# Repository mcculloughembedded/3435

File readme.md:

# The 3435
The *3435* is a 34 key split keyboard inspired by the [Clog V3](https://sammohr.dev/keyboards).
I have used it daily in a professional setting for more than a year.

## Features
* 34 key split
* Low profile - only 18mm from top of keycap to desk (including feet)
* Kailh Choc V1 low profile switches
* MX standard key spacing
* Ortholinear
* Angled columns
* Vertical key staggering
* Pinky cluster
* Two key thumb cluster
* Wired USB-C to PC
* Integrated microcontroller (ATMega32u4)
* Fully enclosed case

# Table of Contents
* [Order PCBs](./instructions/order.md)
* [Program](./instructions/program.md)
* [Assemble](./instructions/build.md)
* [Bill of Materials](./instructions/bill-of-materials.md)

# What's With the Name?
3435 is my favourite number.
It is the only known number where if one raises each digit to the power of itself, then adds the results, one gets back the original number.

That is <br/>
$$3^3 + 4^4 + 3^3 + 5^5 = 3435$$

See [Matt Parker's talk](https://www.youtube.com/watch?v=wt5cRQY8F30) for a more in depth discussion.

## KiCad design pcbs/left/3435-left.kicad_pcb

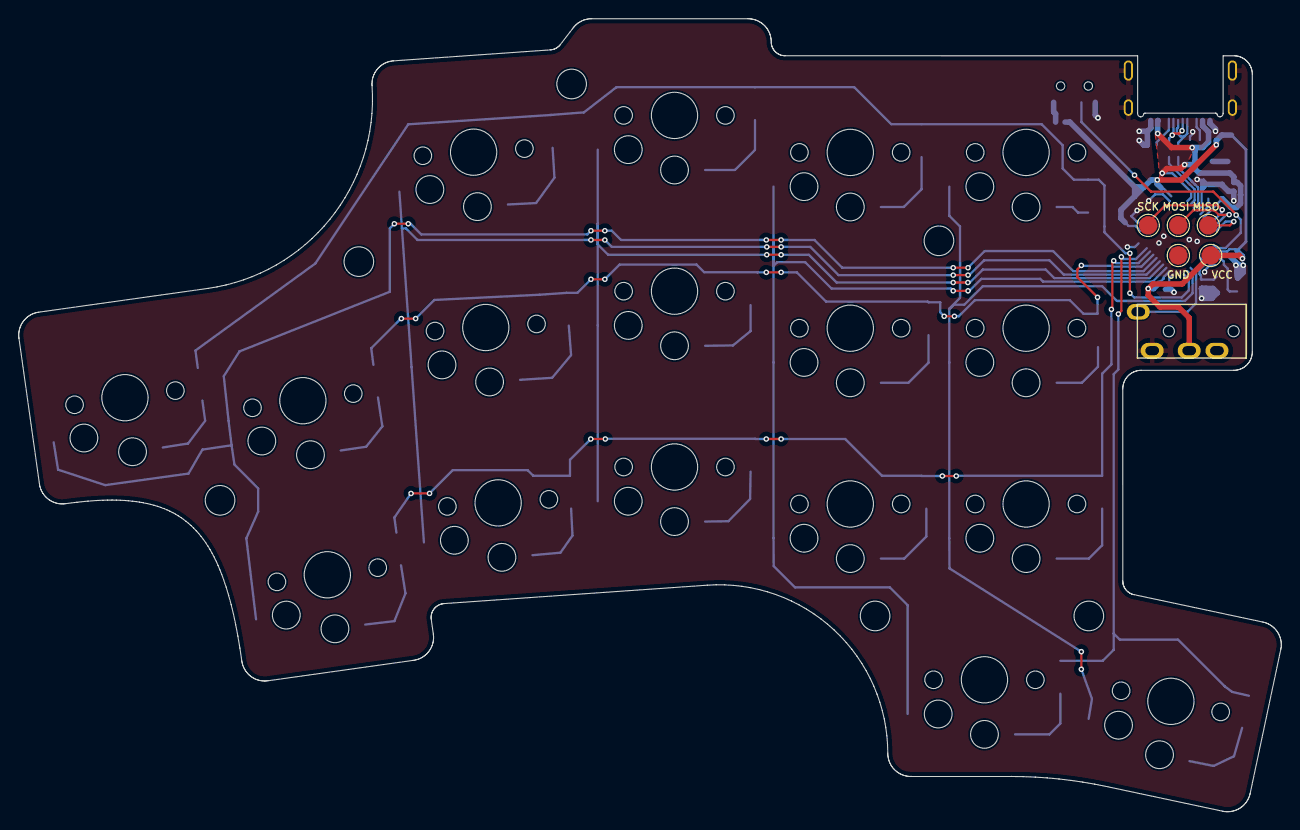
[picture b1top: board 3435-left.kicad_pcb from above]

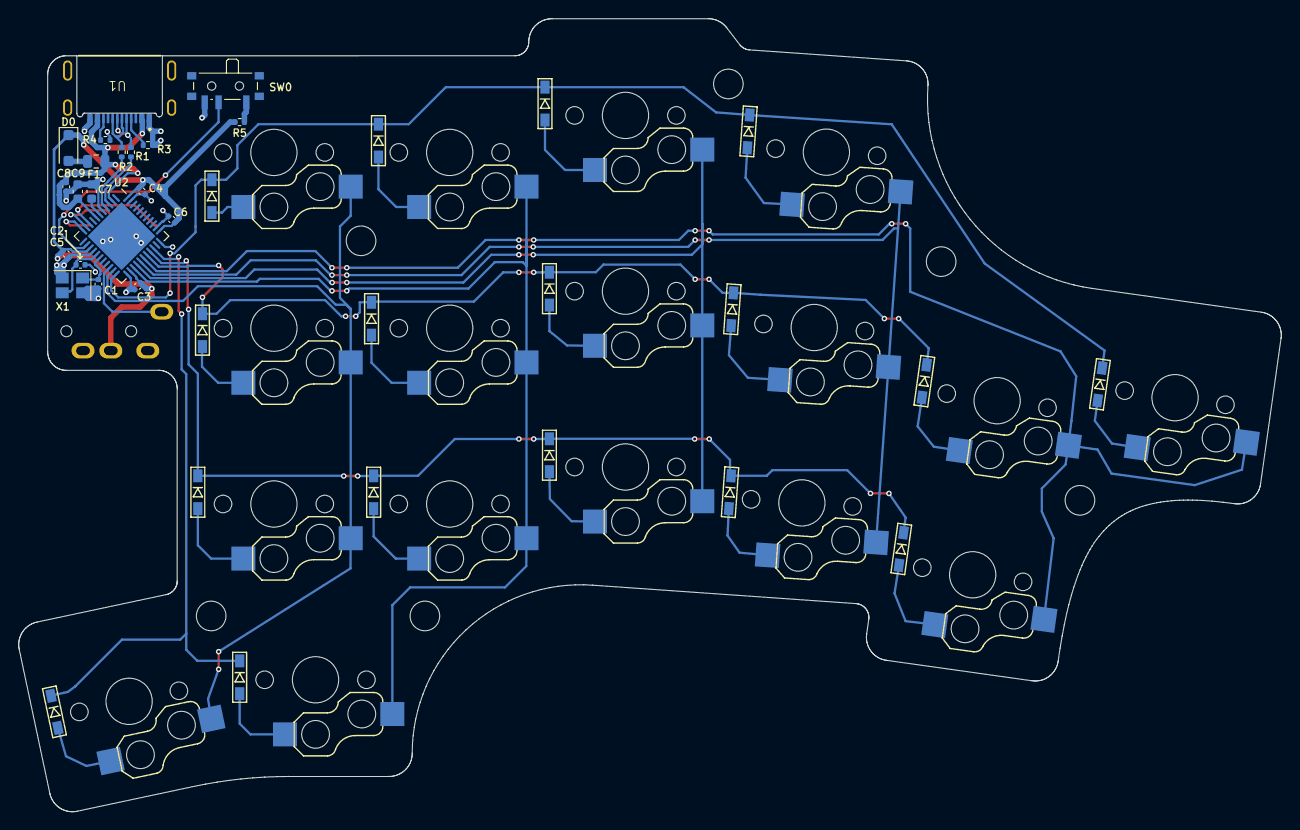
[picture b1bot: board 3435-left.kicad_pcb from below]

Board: 4 copper layers, 136.5 x 85.7 mm, 66 parts (37 on the bottom side), 45 nets.

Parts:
C1, C2: 12p; C_0402_1005Metric
C3, C4, C5, C6, C8: 0u1; C_0402_1005Metric
C7: 1u; C_0603_1608Metric
C9: 4u7; C_0603_1608Metric
D1, D2, D3, D4, D5, D6, D7, D8, D9, D10, D11, D12, D13, D14, D16, D17, D18: D; D3_SMD_v2
D15: D_Schottky; D_SOD-123F
F1: 500mA; Fuse_0805_2012Metric
H1, H2, H3, H4, H5, H6: MountingHole; MountingHole_3.2mm_M3
J1: MJ-4PP-9; MJ-4PP-9_1side
R1, R2: 22; R_0402_1005Metric
R3, R4: 5k1; R_0402_1005Metric
R5: 10k; R_0402_1005Metric
SW1, SW2, SW3, SW4, SW5, SW6, SW7, SW8, SW9, SW10, SW11, SW12, SW13, SW14, SW15, SW16, SW17: SW_PUSH; ChocV1_V2_Hotswap
SW18: SW_SPDT; SW_SPDT_PCM12
TP1, TP2, TP3, TP4, TP5: TestPoint; TestPoint_Pad_D2.0mm
U1: usb-mid-mount
U2: ATmega32U4-M; QFN-44-1EP_7x7mm_P0.5mm_EP5.2x5.2mm
X1: 16MHz; Crystal_SMD_SeikoEpson_FA238-4Pin_3.2x2.5mm

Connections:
/COL1: SW15.1, SW16.1, SW17.1, U2.28 (PB4)
/COL2: SW12.1, SW13.1, SW14.1, U2.27 (PD7)
/COL3: SW9.1, SW10.1, SW11.1, U2.26 (PD6)
/COL4: SW5.1, SW6.1, SW7.1, SW8.1, U2.25 (PD4)
/COL5: SW1.1, SW2.1, SW3.1, SW4.1, U2.21 (PD3)
/D+: R2.2, U2.4 (D+)
/D-: R1.1, U2.3 (D-)
/MISO: TP1.1, U2.11 (PB3)
/MOSI: TP4.1, U2.10 (PB2)
/RAW: D15.2 (A), F1.2
/RESET: SW18.2 (B), U2.13 (~RESET)
/ROW0: D1.1 (K), D5.1 (K), D9.1 (K), D12.1 (K), D16.1 (K), U2.22 (PD5)
/ROW1: D2.1 (K), D6.1 (K), D10.1 (K), D13.1 (K), D17.1 (K), U2.29 (PB5)
/ROW2: D3.1 (K), D7.1 (K), D11.1 (K), D14.1 (K), D18.1 (K), U2.30 (PB6)
/ROW3: D4.1 (K), D8.1 (K), U2.31 (PC6)
/SCK: TP2.1, U2.9 (PB1)
/serial: J1.A, U2.20 (PD2)
GND: C1.2, C2.2, C3.2, C4.2, C5.2, C6.2, C7.2, C8.2, C9.2, J1.D, R3.2, R4.1, SW18.3 (C), TP5.1, U1.A1_B12 (GND), U1.B1_A12 (GND), U1.S1 (SHIELD), U1.S2 (SHIELD), U1.S3 (SHIELD), U1.S4 (SHIELD), U2.5 (UGND), U2.15 (GND), U2.23 (GND), U2.33 (~HWB/PE2), U2.35 (GND), U2.43 (GND), U2.45 (GND), X1.2, X1.4
unnamed: D1.2 (A), SW1.2
unnamed: D2.2 (A), SW2.2
unnamed: D3.2 (A), SW3.2
unnamed: D4.2 (A), SW4.2
unnamed: D5.2 (A), SW5.2
unnamed: D6.2 (A), SW6.2
unnamed: D7.2 (A), SW7.2
unnamed: D8.2 (A), SW8.2
unnamed: D9.2 (A), SW9.2
unnamed: D10.2 (A), SW10.2
unnamed: D11.2 (A), SW11.2
unnamed: D12.2 (A), SW12.2
unnamed: D13.2 (A), SW13.2
unnamed: D14.2 (A), SW14.2
unnamed: D16.2 (A), SW15.2
unnamed: D17.2 (A), SW16.2
unnamed: D18.2 (A), SW17.2
unnamed: R1.2, U1.A7 (D-), U1.B7 (D-)
unnamed: R2.1, U1.A6 (D+), U1.B6 (D+)
unnamed: R5.1, SW18.1 (A)
unnamed: R3.1, U1.A5 (CC)
unnamed: R4.2, U1.B5 (VCONN)
unnamed: C7.1, U2.6 (UCAP)
unnamed: C1.1, U2.17 (XTAL1), X1.1
unnamed: C2.1, U2.16 (XTAL2), X1.3
VBUS: C8.1, C9.1, F1.1, U1.A4_B9 (VBUS), U1.B4_A9 (VBUS), U2.2 (UVCC), U2.7 (VBUS)
VCC: C3.1, C4.1, C5.1, C6.1, D15.1 (K), J1.C, R5.2, TP3.1, U2.14 (VCC), U2.24 (AVCC), U2.34 (VCC), U2.44 (AVCC)

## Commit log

2025-04-03 feat(pcbs): add right side
2025-04-03 chore(.gitignore): ignore kicad generated files
2025-04-03 feat(pcbs): add left side
2025-04-03 chore(*): move mechanical files into separate folder
2025-04-03 feat(readme): add
2025-04-03 fix(readme): fix math expression
2025-04-03 feat(readme): update feature list
2025-04-03 feat(instructions): begin build instructions
2025-04-03 feat(instructions): add
    Getting going. Lots to add...
2025-04-03 fix(build.md): assembly gif
2025-04-03 feat(build.md): add threaded insert assembly gif
2025-04-03 fix(build.md): use the correct gif for threaded insert assembly
2025-04-03 chore(collateral): add threaded-insert-assembly gif
2025-04-03 feat(readme.md): add table of contents
2025-04-03 feat(order/program): add lots of information
2025-04-03 chore(documentation): changes here, changes there, changes everywhere
2025-04-03 feat(readme): add image
2025-04-03 feat(readme): add secondary image
2025-04-03 fix(readme): use correct image for secondary image
2025-04-03 chore(collateral): add raw inkscape svg
2025-04-04 docs(*): cleanup and consistency changes
2025-04-04 docs(bill-of-materials): add
2025-04-04 docs(bill-of-materials): add PCB components
2025-04-04 docs(bill-of-materials): add disclaimer
2025-04-04 docs(*): minor updates
2025-04-04 fix(*.kicad_pcb): add solder mask to USB-C connector
    Problem:
    There was no solder mask on the USB-C connector, so all the pads were
    covered.
    Solution:
    Add the solder mask to the USB-C connectors.
    Note that this was done on each board, as these files no longer have
2025-04-04 docs(order): add section on using datapacks
2025-04-04 docs(order): moar info about datapacks
2025-04-04 fix(order.md): link to innner section
